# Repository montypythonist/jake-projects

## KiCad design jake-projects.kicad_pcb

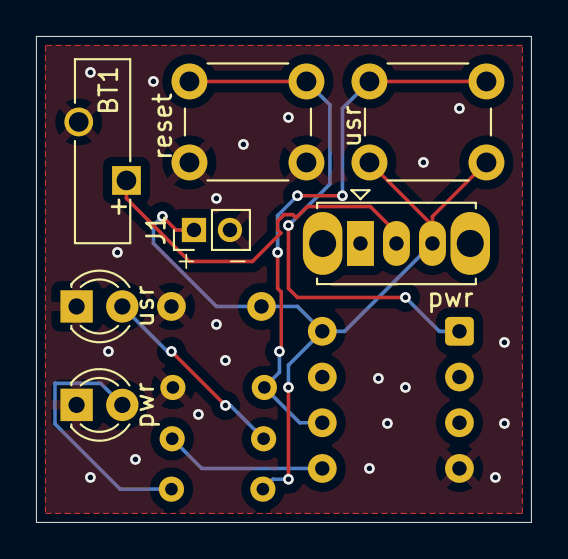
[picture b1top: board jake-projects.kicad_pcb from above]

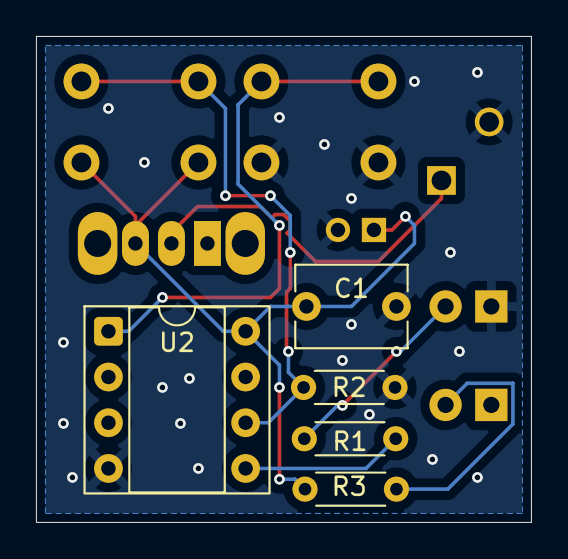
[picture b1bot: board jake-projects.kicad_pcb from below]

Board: 2 copper layers, 27.5 x 27.0 mm, 12 parts (5 on the bottom side), 8 nets.

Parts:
BT1: 3V; Battery_Panasonic_CR1025-VSK_Vertical_CircularHoles
C1: 10uF; C_Disc_D6.0mm_W4.4mm_P5.00mm
J1: Pins; PinHeader_1x02_P2.00mm_Vertical
R1, R2, R3: 1k; R_Axial_DIN0204_L3.6mm_D1.6mm_P5.08mm_Horizontal
U2: ATtiny85-20P; DIP-8_W7.62mm_Socket
pwr: pwr; SW_Slide_SPDT_Straight_CK_OS102011MS2Q
pwr#2: pwr; LED_D3.0mm
reset: reset; SW_PUSH_6mm_H7.3mm
usr: usr; LED_D3.0mm
usr#2: usr; SW_PUSH_6mm_H7.3mm

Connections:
GND: BT1.2 (-), C1.2, J1.2, R2.2, U2.4 (GND), pwr#2.1 (K), reset.2, usr.1 (K)
unnamed: BT1.1 (+), pwr.2 (B)
unnamed: R1.1, usr.2 (A)
unnamed: R3.2, pwr#2.2 (A)
unnamed: R1.2, U2.5 (AREF/PB0)
unnamed: R2.1, U2.6 (PB1), usr#2.1
unnamed: U2.1 (~RESET/PB5), reset.1
VCC: C1.1, J1.1, R3.1, U2.8 (VCC), pwr.3 (C), usr#2.2

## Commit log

2025-12-25 init commit of joy
2025-12-26 Ignoring unnecessary files
2025-12-26 Removing local files
2025-12-27 revised/final draft of schematic + pcb
